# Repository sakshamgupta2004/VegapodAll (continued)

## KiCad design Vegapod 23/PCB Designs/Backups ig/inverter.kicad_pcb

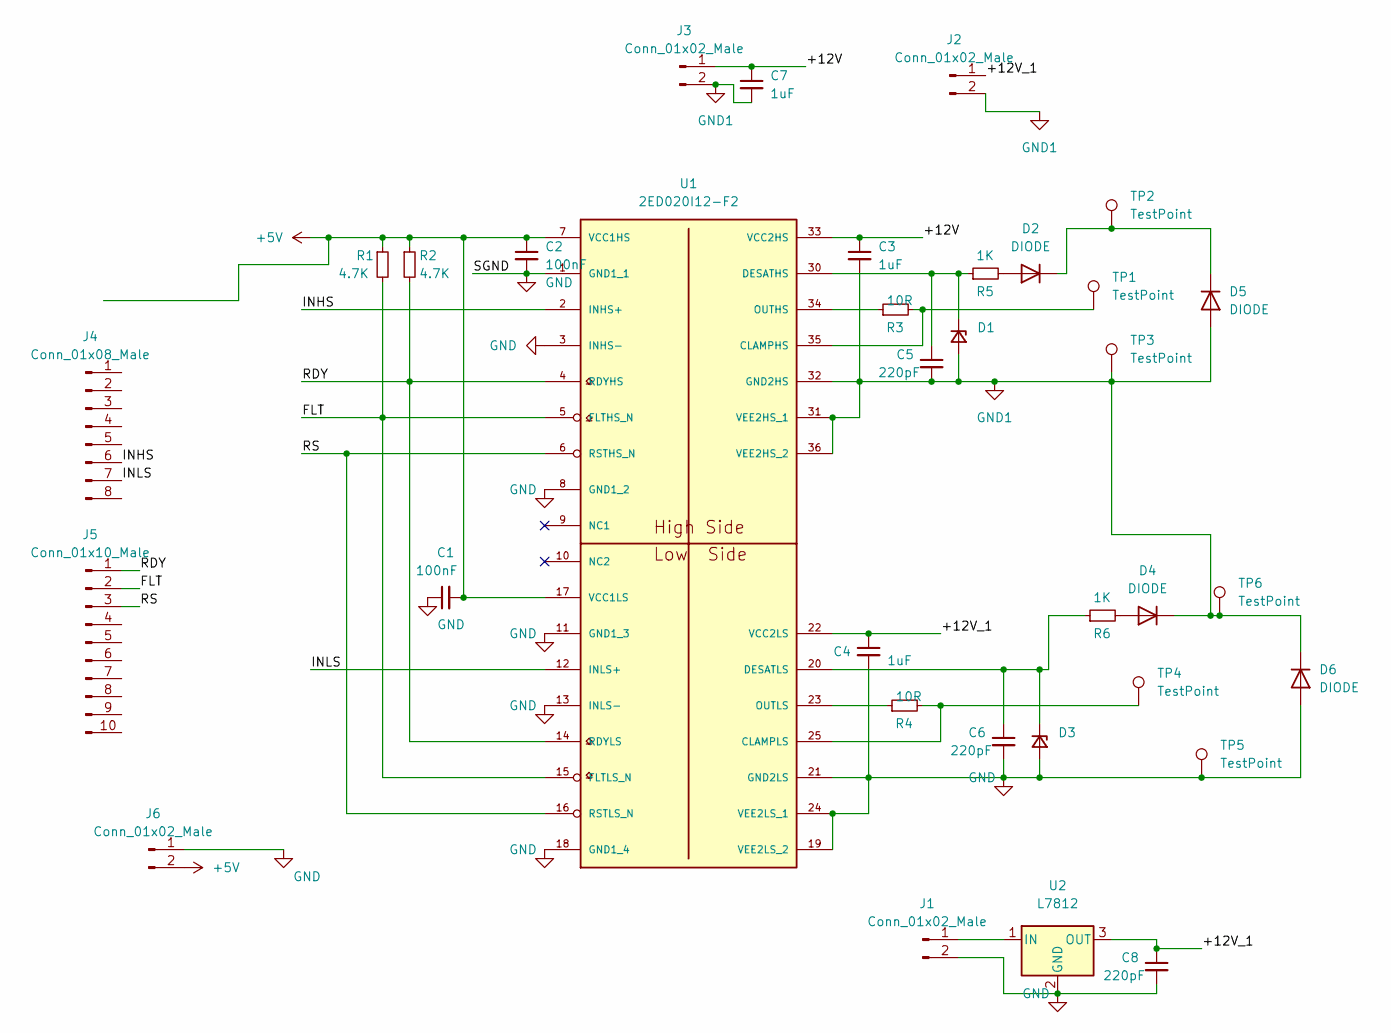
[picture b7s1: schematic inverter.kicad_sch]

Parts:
C1, C2: 100nF; CP_Radial_D14.0mm_P5.00mm
C3, C4, C7: 1uF; CP_Radial_D14.0mm_P5.00mm
C5, C6, C8: 220pF; CP_Radial_D14.0mm_P5.00mm
D1, D3: D_Zener_Small; D_DO-27_P15.24mm_Horizontal
D2, D4, D5, D6: DIODE; D_DO-27_P15.24mm_Horizontal
J1, J2, J3: Conn_01x02_Male; PhoenixContact_MCV_1,5_2-G-5.08_1x02_P5.08mm_Vertical
J4: Conn_01x08_Male; PinHeader_1x08_P2.54mm_Vertical
J5: Conn_01x10_Male; PinHeader_1x10_P2.54mm_Vertical
J6: Conn_01x02_Male; PinHeader_1x02_P2.54mm_Vertical
R1, R2: 4.7K; R_Axial_DIN0411_L9.9mm_D3.6mm_P12.70mm_Horizontal
R3, R4: 10R; R_Axial_DIN0411_L9.9mm_D3.6mm_P12.70mm_Horizontal
R5, R6: 1K; R_Axial_DIN0411_L9.9mm_D3.6mm_P12.70mm_Horizontal
TP1, TP2, TP3, TP4, TP5, TP6: TestPoint; TestPoint_Pad_D4.0mm
U1: 2ED020I12-F2; SOP65P1030X265-36_32N-V
U2: L7812; TO-220-3_Vertical

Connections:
+5V: C1.2, C2.1, J6.2, R1.1, R2.1, U1.7 (VCC1HS), U1.17 (VCC1LS)
/+12V: C3.1, C7.1, J3.1, U1.33 (VCC2HS)
/+12V_1: C4.1, C8.1, J2.1, U1.22 (VCC2LS), U2.3 (OUT)
/FLT: J5.2, R1.2, U1.5 (FLTHS_N), U1.15 (FLTLS_N)
/INHS: J4.6, U1.2 (INHS+)
/INLS: J4.7, U1.12 (INLS+)
/RDY: J5.1, R2.2, U1.4 (RDYHS), U1.14 (RDYLS)
/RS: J5.3, U1.6 (RSTHS_N), U1.16 (RSTLS_N)
GND: C1.1, C2.2, C4.2, C6.2, C8.2, D3.2 (A), D6.1 (A), J1.2, J6.1, TP5.1, U1.1 (GND1_1), U1.3 (INHS-), U1.8 (GND1_2), U1.11 (GND1_3), U1.13 (INLS-), U1.18 (GND1_4), U1.19 (VEE2LS_2), U1.21 (GND2LS), U1.24 (VEE2LS_1), U2.2 (GND)
GND1: C3.2, C5.2, C7.2, D1.2 (A), D4.2 (K), D5.1 (A), D6.2 (K), J2.2, J3.2, TP3.1, TP6.1, U1.31 (VEE2HS_1), U1.32 (GND2HS), U1.36 (VEE2HS_2)
unnamed: C5.1, D1.1 (K), R5.1, U1.30 (DESATHS)
unnamed: C6.1, D3.1 (K), R6.1, U1.20 (DESATLS)
unnamed: D2.1 (A), R5.2
unnamed: D2.2 (K), D5.2 (K), TP2.1
unnamed: D4.1 (A), R6.2
unnamed: J1.1, U2.1 (IN)
unnamed: R3.1, U1.34 (OUTHS)
unnamed: R3.2, TP1.1, U1.35 (CLAMPHS)
unnamed: R4.1, U1.23 (OUTLS)
unnamed: R4.2, TP4.1, U1.25 (CLAMPLS)

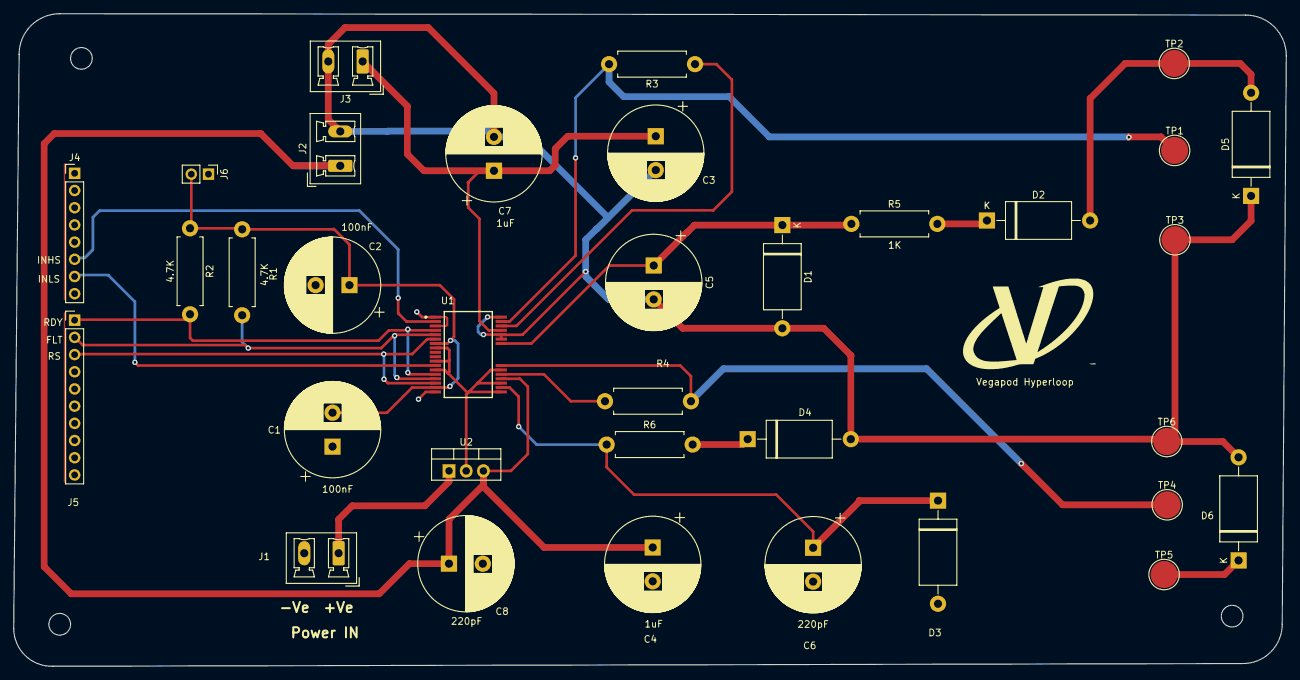
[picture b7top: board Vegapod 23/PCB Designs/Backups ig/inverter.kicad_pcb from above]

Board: 2 copper layers, 188.0 x 96.4 mm, 34 parts (0 on the bottom side), 20 nets.
